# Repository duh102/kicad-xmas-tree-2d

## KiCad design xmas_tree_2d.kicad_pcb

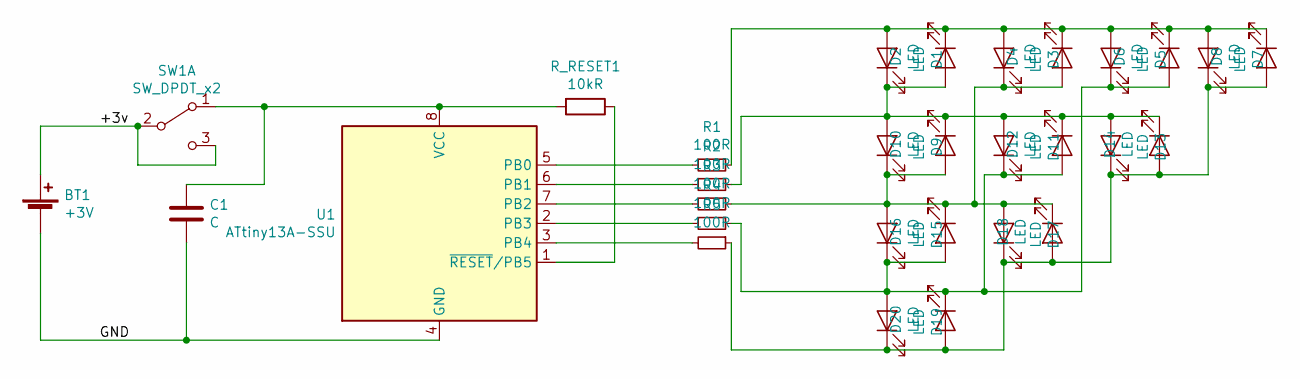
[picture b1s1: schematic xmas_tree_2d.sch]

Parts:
BT1: +3V; BatteryHolder_Keystone_3034_1x20mm
C1: C; C_0805_2012Metric
D1, D2, D3, D4, D5, D6, D7, D8, D9, D10, D11, D12, D13, D14, D15, D16, D17, D18, D19, D20: LED; LED_0805_2012Metric
R1, R2, R3, R4, R5: 100R; R_0805_2012Metric
R_RESET1: 10kR; R_0805_2012Metric
SW1: SW_DPDT_x2; SW_Slide_1P2T_CK_OS102011MS2Q
U1: ATtiny13A-SSU; SOIC-8_3.9x4.9mm_P1.27mm

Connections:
/+3v: BT1.1 (+), SW1.2 (B), SW1.3 (C)
/GND: BT1.2 (-), C1.2, U1.4 (GND)
unnamed: C1.1, R_RESET1.2, SW1.1 (A), U1.8 (VCC)
unnamed: D1.1 (K), D2.2 (A), D9.2 (A), D10.1 (K), D11.2 (A), D12.1 (K), D13.2 (A), D14.1 (K), R2.1
unnamed: D1.2 (A), D2.1 (K), D3.2 (A), D4.1 (K), D5.2 (A), D6.1 (K), D7.2 (A), D8.1 (K), R1.1
unnamed: D3.1 (K), D4.2 (A), D9.1 (K), D10.2 (A), D15.2 (A), D16.1 (K), D17.2 (A), D18.1 (K), R3.1
unnamed: D5.1 (K), D6.2 (A), D11.1 (K), D12.2 (A), D15.1 (K), D16.2 (A), D19.2 (A), D20.1 (K), R4.1
unnamed: D7.1 (K), D8.2 (A), D13.1 (K), D14.2 (A), D17.1 (K), D18.2 (A), D19.1 (K), D20.2 (A), R5.1
unnamed: R1.2, U1.5 (PB0)
unnamed: R2.2, U1.6 (PB1)
unnamed: R3.2, U1.7 (PB2)
unnamed: R4.2, U1.2 (PB3)
unnamed: R5.2, U1.3 (PB4)
unnamed: R_RESET1.1, U1.1 (~RESET~/PB5)

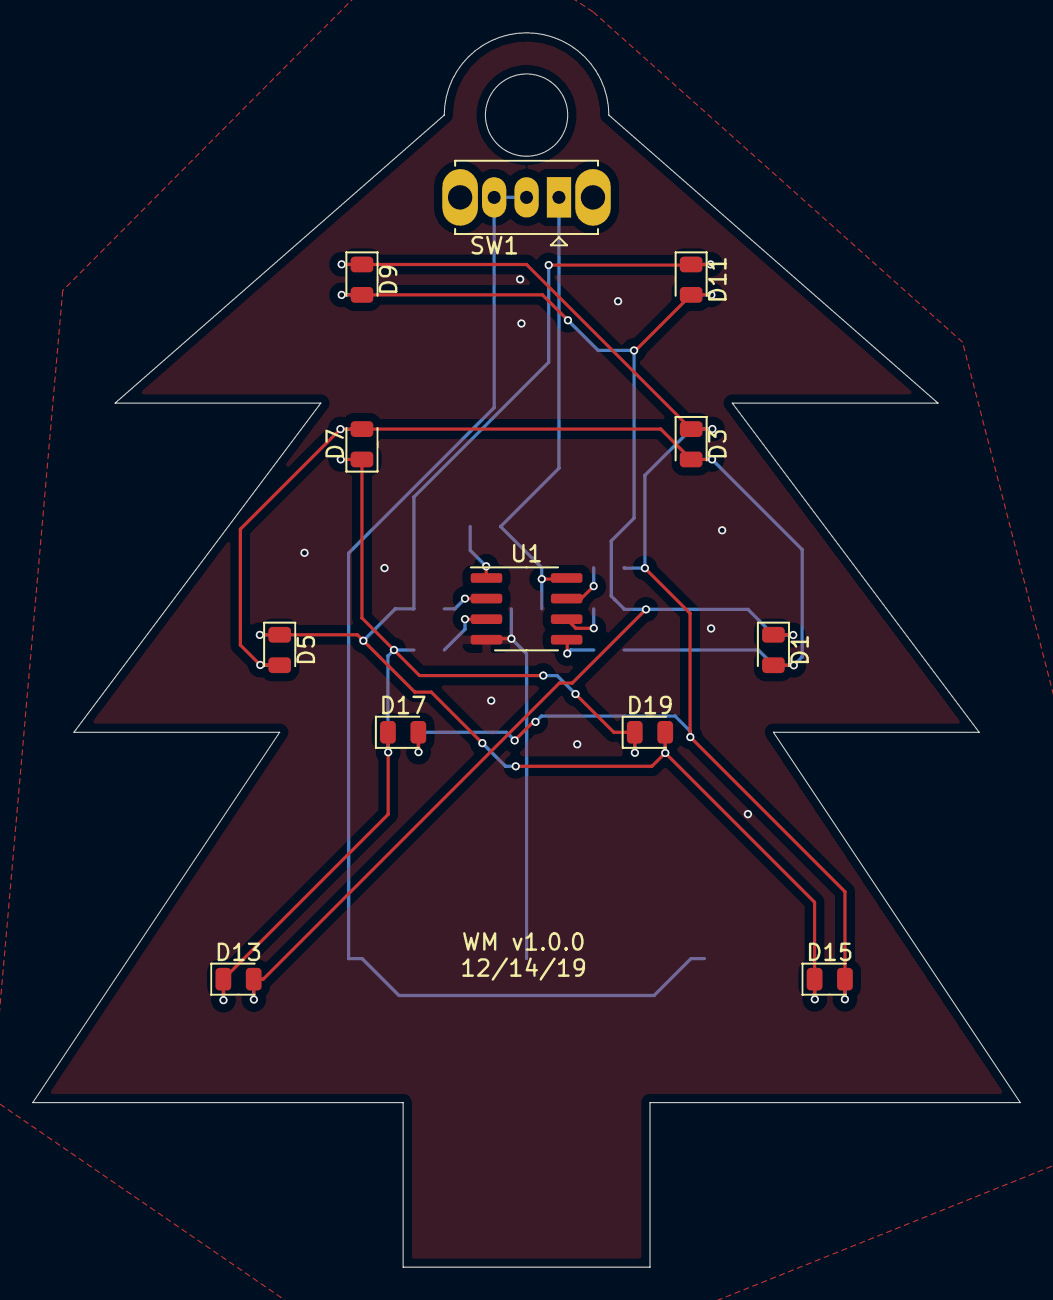
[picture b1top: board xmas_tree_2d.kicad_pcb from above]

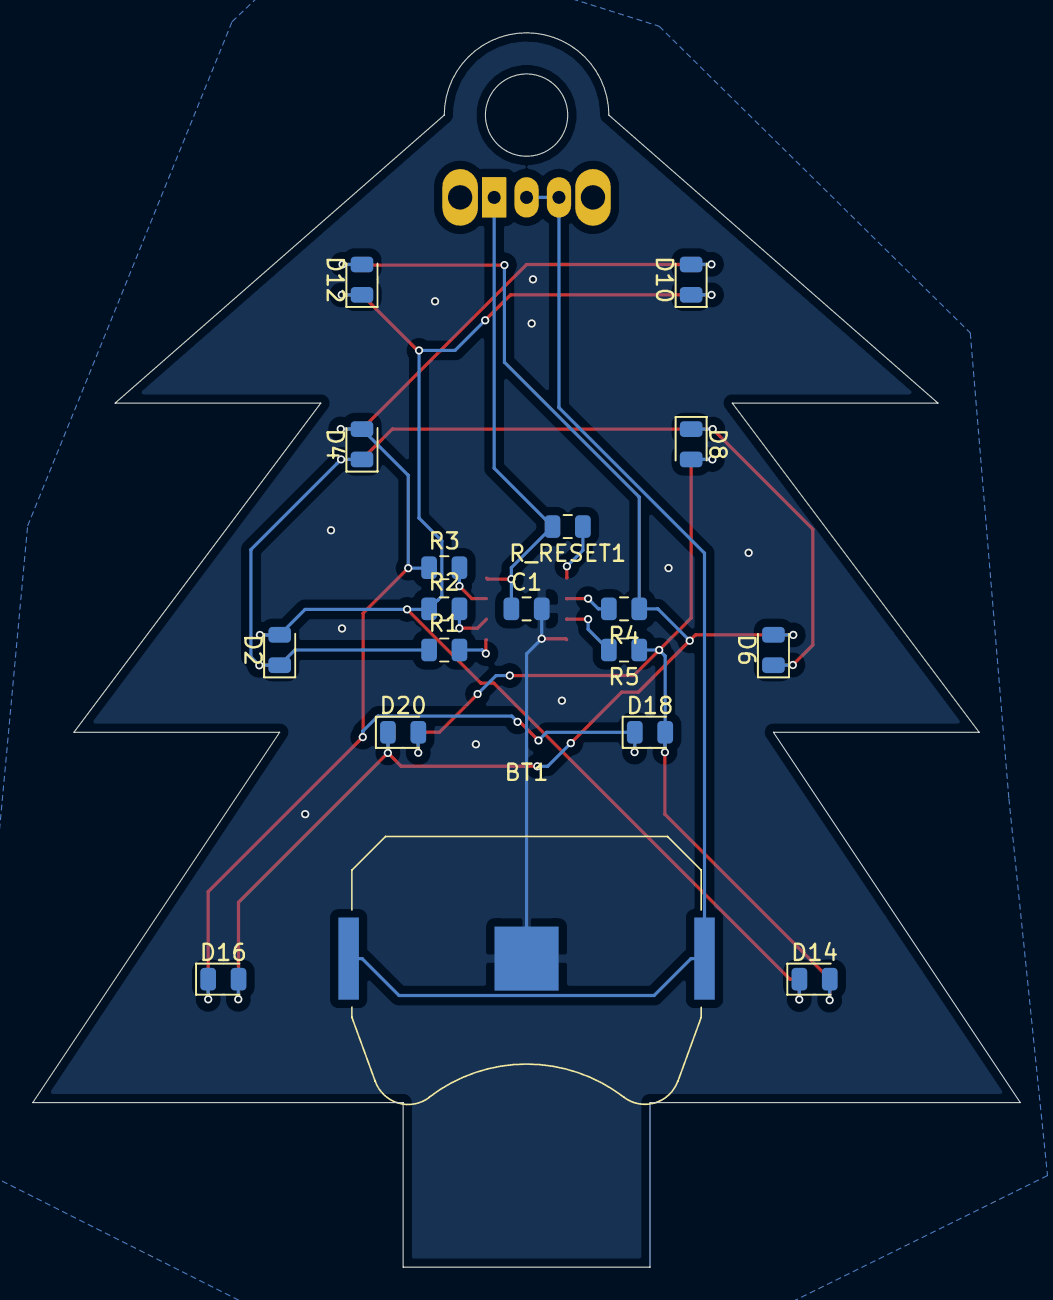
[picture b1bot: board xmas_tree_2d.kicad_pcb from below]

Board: 2 copper layers, 61.0 x 76.2 mm, 30 parts (18 on the bottom side), 14 nets.

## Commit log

2020-12-09 Recue lib
